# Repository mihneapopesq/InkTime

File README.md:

# InkTime

## Block Diagram
The system architecture centers on the nRF52840 SoC for wireless connectivity, with power stabilized at 3.3V via an RT6160 buck-boost regulator. It integrates a LiPo battery with USB-C charging alongside an e-paper display, IMU, fuel gauge, and haptic feedback.

## Bill of Materials (BOM)

|Component|JLC Part #|Package|Description|Datasheet|
| :--- | :--- | :--- | :--- | :--- |
|SJ1|N/A|Solder Jumper (Copper feature - leave open)|SMD solder JUMPER|N/A|
|R2, R3, R4|[C3920633](https://www.lcsc.com/product-detail/C3920633.html)|0201|7.68k 0201 Thin Film Surface Mount Fixed Resistor +/-0.5% 0.031W CPF0201D7K68C1|[datasheet](https://wmsc.lcsc.com/wmsc/upload/file/pdf/v2/lcsc/2404081048_TE-Connectivity-CPF0201B511RE1_C3920633.pdf)|
|C23, C27, C34, C42|[C21012218](https://www.lcsc.com/product-detail/C21012218.html)|-|Check availability|[datasheet](https://jlc-prod-smt.oss-eu-central-1.aliyuncs.com/smtDataManualFile/8603520985945550848-C21012218.pdf?response-content-disposition=attachment%3B%20filename%3DC21012218.pdf%3B%20filename%2A%3DUTF-8%27%27C21012218.pdf&x-oss-date=20260407T205848Z&x-oss-expires=1800&x-oss-security-token=CAISgAN1q6Ft5B2yfSjIr5r9Dd2HhJt1xpCRZnzhgHQ0Psp9nrTKiTz2IHhMdHJsAOodtv0%2FmmhT6PkclqRLcbhpcmfjV%2BZHzLB8qYoRtS1%2F4J7b16cNrbH4M4H6aXeirtuwDsz9SNTCALjPD3nPii50x5bjaDymRCbLGJaViJlhHLN1Ow6jdmhpCctxLAlvo9NgFxm3D%2Fu2NQPwiWf9FVdhvhEG6Vly8qOi2MaRmFy8yFTx0b0SvJ%2BjYMrmPctoN9JnSdC5mfdzau3a1TJ84gRD0a5wkaVA1zbDs5bfISEIuUzebreLqY03dV4mOvdqIcMe8qigz88fk%2FfIioH6xyxKOexoSCnFTOiiupCcQLPyao9jLu6iayqViY7QaIOTqQohZmkAMwVOasAsI3Ngh4zF97Qt0cVNkXO9gWfLI8DtuMleWoolCMBMoNHD0eS19jklBdzSlusJRAJJUVBflCeKEaRNSAd3WGhEfM2%2BBt4QT30w5N2u00S8OSMIfXAg5qKWD5sagAGsz%2FZUSUxHdlmxVPmipF%2FTcZWs78wlHh10XRuVSQAFwkjbrT5Hik%2Bt6g43igoBe9p%2FcAdU6beRw%2F0OV8Ul08RsL45K5wTZwHFsbzFcwqB3eAqV0VruhFdx%2FHGC73AK3f%2BS3e6Qh1%2F1xoEQbmetO%2F%2BEcdyt%2BmwKiZrCa5Agq9keuCAA&x-oss-signature-version=OSS4-HMAC-SHA256&x-oss-credential=STS.NYHFg3iDTqRzdZPdta2EQqqak%2F20260407%2Feu-central-1%2Foss%2Faliyun_v4_request&x-oss-signature=20ddec61a1b664f2d44439cb342bbd932d8702b658f2816e0dfb7eb77563430a)|
|EPD_C5|[C9900156064](https://www.lcsc.com/product-detail/C9900156064.html)|201|Generic chip capacitor|[datasheet](https://ds.yuden.co.jp/TYCOMPAS/or/download?pn=MLAST063SCG681JFNA01&fileType=CA)|
|R1_EP_DR|[C3920633](https://www.lcsc.com/product-detail/C3920633.html)|0201|7.68k 0201 Thin Film Surface Mount Fixed Resistor +/-0.5% 0.031W CPF0201D7K68C1|[datasheet](https://wmsc.lcsc.com/wmsc/upload/file/pdf/v2/lcsc/2404081048_TE-Connectivity-CPF0201B511RE1_C3920633.pdf)|
|C15|[C9900156064](https://www.lcsc.com/product-detail/C9900156064.html)|201|Generic chip capacitor|[datasheet](https://ds.yuden.co.jp/TYCOMPAS/or/download?pn=MLAST063SCG681JFNA01&fileType=CA)|
|C5, C7, C8, C12, C19|[C9900156064](https://www.lcsc.com/product-detail/C9900156064.html)|201|Generic chip capacitor|[datasheet](https://ds.yuden.co.jp/TYCOMPAS/or/download?pn=MLAST063SCG681JFNA01&fileType=CA)|
|C11|[C9900156064](https://www.lcsc.com/product-detail/C9900156064.html)|201|Generic chip capacitor|[datasheet](https://ds.yuden.co.jp/TYCOMPAS/or/download?pn=MLAST063SCG681JFNA01&fileType=CA)|
|R2_EP_DR, R9, R_PWR_EPD|[C3920633](https://www.lcsc.com/product-detail/C3920633.html)|0201|7.68k 0201 Thin Film Surface Mount Fixed Resistor +/-0.5% 0.031W CPF0201D7K68C1|[datasheet](https://wmsc.lcsc.com/wmsc/upload/file/pdf/v2/lcsc/2404081048_TE-Connectivity-CPF0201B511RE1_C3920633.pdf)|
|R5, R7, R8|[C3920633](https://www.lcsc.com/product-detail/C3920633.html)|0201|7.68k 0201 Thin Film Surface Mount Fixed Resistor +/-0.5% 0.031W CPF0201D7K68C1|[datasheet](https://wmsc.lcsc.com/wmsc/upload/file/pdf/v2/lcsc/2404081048_TE-Connectivity-CPF0201B511RE1_C3920633.pdf)|
|C1-EP-DR|[C9900156064](https://www.lcsc.com/product-detail/C9900156064.html)|201|Generic chip capacitor|[datasheet](https://ds.yuden.co.jp/TYCOMPAS/or/download?pn=MLAST063SCG681JFNA01&fileType=CA)|
|C24, C39|[C9900179830](https://www.lcsc.com/product-detail/C9900179830.html)|402|0402 (1005 Metric)|N/A|
|L2|[C12669](https://www.lcsc.com/product-detail/C12669.html)|402|Generic chip inductor|[datasheet](https://www.lcsc.com/datasheet/lcsc_datasheet_2304140030_Murata-Electronics-LQG15HS27NJ02D_C12669.pdf)|
|C1, C2, C17, C18|[C9900156064](https://www.lcsc.com/product-detail/C9900156064.html)|201|Generic chip capacitor|[datasheet](https://ds.yuden.co.jp/TYCOMPAS/or/download?pn=MLAST063SCG681JFNA01&fileType=CA)|
|L3|[C12669](https://www.lcsc.com/product-detail/C12669.html)|402|Generic chip inductor|[datasheet](https://www.lcsc.com/datasheet/lcsc_datasheet_2304140030_Murata-Electronics-LQG15HS27NJ02D_C12669.pdf)|
|C3, C4|[C9900156064](https://www.lcsc.com/product-detail/C9900156064.html)|201|Generic chip capacitor|[datasheet](https://ds.yuden.co.jp/TYCOMPAS/or/download?pn=MLAST063SCG681JFNA01&fileType=CA)|
|C29, C30, C31, C32, C37, C38|[C3920633](https://www.lcsc.com/product-detail/C3920633.html)|0201|7.68k 0201 Thin Film Surface Mount Fixed Resistor +/-0.5% 0.031W CPF0201D7K68C1|[datasheet](https://wmsc.lcsc.com/wmsc/upload/file/pdf/v2/lcsc/2404081048_TE-Connectivity-CPF0201B511RE1_C3920633.pdf)|
|EPD_C1, EPD_C2, EPD_C6, EPD_C7, EPD_C8, EPD_C9, EPD_C10, EPD_C11, EPD_C12|[C9900156064](https://www.lcsc.com/product-detail/C9900156064.html)|201|Generic chip capacitor|[datasheet](https://ds.yuden.co.jp/TYCOMPAS/or/download?pn=MLAST063SCG681JFNA01&fileType=CA)|
|R_TYPE_SEL|[C3920633](https://www.lcsc.com/product-detail/C3920633.html)|0201|7.68k 0201 Thin Film Surface Mount Fixed Resistor +/-0.5% 0.031W CPF0201D7K68C1|[datasheet](https://wmsc.lcsc.com/wmsc/upload/file/pdf/v2/lcsc/2404081048_TE-Connectivity-CPF0201B511RE1_C3920633.pdf)|
|SW_DN, SW_ENT, SW_UP|[C569760](https://www.lcsc.com/product-detail/C569760.html)|SMD,3.9x2.9mm|-40℃~+85℃ 1.6N 1.6mm 15V 2.9mm 20mA 3.9mm 500,000 Cycles IP67 J-Lead Rectangular Button SPST Surface Mount,Vertical White With Bracket SMD,3.9x2.9mm Tactile Switches ROHS|[datasheet](https://wmsc.lcsc.com/wmsc/upload/file/pdf/v2/lcsc/2301111010_PANASONIC-EVPAKE31A_C569760.pdf)|
|Q1|[C2564](https://www.lcsc.com/product-detail/C2564.html)|TO-220AB|-55℃~+175℃ 1 P-Channel 180nC@10V 200W 20mΩ@10V 3.4nF 4V 55V 640pF 74A P-Channel TO-220AB MOSFETs ROHS|[datasheet](https://www.lcsc.com/datasheet/lcsc_datasheet_1809041724_Infineon-Technologies-IRF4905PBF_C2564.pdf)|
|C25, C33|[C9900179830](https://www.lcsc.com/product-detail/C9900179830.html)|402|0402 (1005 Metric)|N/A|
|ANT1|[C2917717](https://www.lcsc.com/product-detail/C2917717.html)|1206|-45℃~+125℃ 0.5dBi 1.3mm 1.6mm 100MHz 2.45GHz 2W 3.2mm 50Ω Patch Antenna 1206 Antennas ROHS|[datasheet](https://www.lcsc.com/datasheet/lcsc_datasheet_2404021210_Johanson-Dielectrics-2450AT18B100E_C2917717.pdf)|
|L1|[C12669](https://www.lcsc.com/product-detail/C12669.html)|402|Generic chip inductor|[datasheet](https://www.lcsc.com/datasheet/lcsc_datasheet_2304140030_Murata-Electronics-LQG15HS27NJ02D_C12669.pdf)|
|X2|[C32346](https://www.lcsc.com/product-detail/C32346.html)|SMD3215-2P|-40℃~+85℃ 12.5pF 32.768kHz 70kΩ Crystal Oscillator ±20ppm SMD3215-2P Crystals ROHS|[datasheet](https://www.lcsc.com/datasheet/lcsc_datasheet_2404180925_Seiko-Epson-Q13FC13500004_C32346.pdf)|
|X1|[C9009](https://www.lcsc.com/product-detail/C9009.html)|SMD3225-4P|-40℃~+85℃ 12pF 32MHz Crystal Oscillator ±10ppm ±20ppm SMD3225-4P Crystals ROHS|[datasheet](https://www.lcsc.com/datasheet/lcsc_datasheet_2403291504_YXC-Crystal-Oscillators-X322532MOB4SI_C9009.pdf)|
|R17, R18|[C3920633](https://www.lcsc.com/product-detail/C3920633.html)|0201|7.68k 0201 Thin Film Surface Mount Fixed Resistor +/-0.5% 0.031W CPF0201D7K68C1|[datasheet](https://wmsc.lcsc.com/wmsc/upload/file/pdf/v2/lcsc/2404081048_TE-Connectivity-CPF0201B511RE1_C3920633.pdf)|
|C43|[C9900156064](https://www.lcsc.com/product-detail/C9900156064.html)|201|Generic chip capacitor|[datasheet](https://ds.yuden.co.jp/TYCOMPAS/or/download?pn=MLAST063SCG681JFNA01&fileType=CA)|
|C2-EP-DR|[C9900156064](https://www.lcsc.com/product-detail/C9900156064.html)|201|Generic chip capacitor|[datasheet](https://ds.yuden.co.jp/TYCOMPAS/or/download?pn=MLAST063SCG681JFNA01&fileType=CA)|
|C6, C14, C20, C21|[C9900156064](https://www.lcsc.com/product-detail/C9900156064.html)|201|Generic chip capacitor|[datasheet](https://ds.yuden.co.jp/TYCOMPAS/or/download?pn=MLAST063SCG681JFNA01&fileType=CA)|
|C16|[C9900156064](https://www.lcsc.com/product-detail/C9900156064.html)|201|Generic chip capacitor|[datasheet](https://ds.yuden.co.jp/TYCOMPAS/or/download?pn=MLAST063SCG681JFNA01&fileType=CA)|
|J1|[C122434](https://www.lcsc.com/product-detail/C122434.html)|SMD,P=0.5mm,Surface Mount，Right Angle|FFC & FPC Connectors 0.5mm FPC RA SMT Dual Contact 24Ckt|[datasheet](https://www.molex.com/content/dam/molex/molex-dot-com/products/automated/en-us/salesdrawingpdf/503/503480/5034802400_sd.pdf)|
|R1_USB, R2_USB|[C3920633](https://www.lcsc.com/product-detail/C3920633.html)|0201|7.68k 0201 Thin Film Surface Mount Fixed Resistor +/-0.5% 0.031W CPF0201D7K68C1|[datasheet](https://wmsc.lcsc.com/wmsc/upload/file/pdf/v2/lcsc/2404081048_TE-Connectivity-CPF0201B511RE1_C3920633.pdf)|
|L5|[C1329646](https://www.lcsc.com/product-detail/C1329646.html)|SMD,4.8x4.8mm|1.6A 1.6A 4.7uH 41.4mΩ AEC-Q200 ±30% SMD,4.8x4.8mm Power Inductors ROHS|[datasheet](https://wmsc.lcsc.com/wmsc/upload/file/pdf/v2/lcsc/2304140030_BOURNS-SRR4828A-4R7Y_C1329646.pdf)|
|C9|[C9900156064](https://www.lcsc.com/product-detail/C9900156064.html)|201|Generic chip capacitor|[datasheet](https://ds.yuden.co.jp/TYCOMPAS/or/download?pn=MLAST063SCG681JFNA01&fileType=CA)|
|IC3|[C189517](https://www.lcsc.com/product-detail/C189517.html)|LGA-12(2x2)|Accelerometers Triaxial low-g 12bit Acceleration Sensor|[datasheet](https://www.lcsc.com/datasheet/C189517.pdf)|
|IC1|[C3682423](https://www.lcsc.com/product-detail/C3682423.html)|DSBGA-8(1.1x1.6)|Charger IC Lithium Ion/Polymer, Lithium Iron Phosphate 8-DSBGA (1.6x1.1)|[datasheet](https://www.ti.com/cn/lit/ds/symlink/bq25180.pdf?ts=1775594237116)|
|IC2|[C81079](https://www.lcsc.com/product-detail/C81079.html)|DSBGA-9|Haptic Driver for ERM/LRA with Built-In Library and Smart Loop Architecture|[datasheet](https://www.ti.com/cn/lit/gpn/drv2605)|
|L7|[C5832368](https://www.lcsc.com/product-detail/C5832368.html)|1008|13mΩ 470nH 6.5A 7.5A ±20% 1008 Power Inductors ROHS|[datasheet](https://wmsc.lcsc.com/wmsc/upload/file/pdf/v2/lcsc/2306021632_cjiang--Changjiang-Microelectronics-Tech-FTC252012SR47MBCA_C5832368.pdf)|
|TP (Test Pads)|N/A|N/A|Test pad|N/A|
|J4|[C709357](https://www.lcsc.com/product-detail/C709357.html)|SMD|-40℃~+85℃ 1 10,000 cycles 16P 30V 3A 7.81mm Female Surface Mount, Right Angle Type-C SMD USB Connectors ROHS|[datasheet](https://www.lcsc.com/datasheet/lcsc_datasheet_2404191039_Shenzhen-Kinghelm-Elec-KH-TYPE-C-16P_C709357.pdf)|
|U2|[C2682616](https://www.lcsc.com/product-detail/C2682616.html)|DFN-8-EP(2x2)|-40℃~+85℃ 1 2.5V~4.5V 3uA I2C Lithium Battery DFN-8-EP(2x2) Battery Management ROHS|[datasheet](https://www.lcsc.com/datasheet/lcsc_datasheet_2410121738_Analog-Devices-Inc--Maxim-Integrated-MAX17048G-T10_C2682616.pdf)|
|D2, D4, D5|[C82046](https://www.lcsc.com/product-detail/C82046.html)|SOD-123|ON SEMICONDUCTOR - MBR0530 - DIODE, SCHOTTKY, 0.5A, 30V, SOD-123|[datasheet](https://www.lcsc.com/datasheet/lcsc_datasheet_2304140030_onsemi-MBR0530T1G_C82046.pdf)|
|C10, C13, C22|[C9900156064](https://www.lcsc.com/product-detail/C9900156064.html)|201|Generic chip capacitor|[datasheet](https://ds.yuden.co.jp/TYCOMPAS/or/download?pn=MLAST063SCG681JFNA01&fileType=CA)|
|U1|[C3606653](https://www.lcsc.com/product-detail/C3606653.html)|QFN-48(6x6)|nRF52840|[datasheet](https://www.lcsc.com/datasheet/C3606653.pdf)|
|IC9|[C7065276](https://www.lcsc.com/product-detail/C7065276.html)|WLCSP-15B(2.3x1.4)|Buck-Boost Regulator Positive Output Step-Up/Step-Down I2C DC-DC Controller IC 15-WL-CSP (BSC) (1.4x2.3)|[datasheet](https://wmsc.lcsc.com/wmsc/upload/file/pdf/v2/lcsc/2312271436_Richtek-Tech-RT6160AWSC_C7065276.pdf)|
|Q3|[C469327](https://www.lcsc.com/product-detail/C469327.html)|SOT-323|MOSFET N-Ch 30V 1.5A TrenchFET SC70 Vishay Si1308EDL-T1-GE3 N-channel MOSFET Transistor, 1.5 A, 30 V, 3-Pin SC-70|[datasheet](https://www.lcsc.com/datasheet/lcsc_datasheet_1912202016_Vishay-Intertech-SI1308EDL-T1-GE3_C469327.pdf)|
|J2|[C90533](https://www.lcsc.com/product-detail/C90533.html)|P=1mm|CABLE ADAPTER 6 POS|[datasheet](https://wmsc.lcsc.com/wmsc/upload/file/pdf/v2/lcsc/1810141506_LX-FFC6P1-0mm7CM_C90533.pdf)|
|D3|[C2969755](https://www.lcsc.com/product-detail/C2969755.html)|SOT-23-6L|Low Cap. ESD Protection Auto SOT-23-6 STMicroelectronics USBLC6-2SC6Y, Dual Uni-Directional TVS Diode Array, 6-Pin SOT-23|[datasheet](https://wmsc.lcsc.com/wmsc/upload/file/pdf/v2/lcsc/2211080730_STMicroelectronics-USBLC6-2SC6Y_C2969755.pdf)|

## Hardware Functionality & Technical Architecture

The **InkTime** platform is an ultra-low-power wearable built around the **Nordic nRF52840 SoC**. The design focuses on maximizing battery autonomy through an E-Ink interface and advanced power management, ensuring the device remains functional for weeks on a single charge.

### 1. Core Processing Unit
The **nRF52840 (ARM Cortex-M4F @ 64 MHz)** serves as the system's brain. It was selected for its:
* **Connectivity:** Native Bluetooth 5.4 LE support for smartphone syncing.
* **I/O Versatility:** Integrated USB, SPI, and I2C peripherals to manage all sub-systems.
* **Efficiency:** Advanced "Deep Sleep" modes (sub-10 µA) and a dedicated 32.768 kHz crystal for accurate low-power timing.

### 2. Power & Energy Management
The power tree is designed to extract maximum energy from the **250 mAh Li-Po battery**:
* **Charging:** A **BQ25180 PMIC** manages the CC/CV charging cycle via **USB-C**, providing overvoltage and thermal protection.
* **Regulation:** The **RT6160 Buck-Boost converter** maintains a stable **3.3V** rail even as the battery voltage drops toward 3.0V, outperforming standard LDOs.
* **Fuel Gauge:** The **MAX17048G** monitor provides high-precision State of Charge (SoC) data via I2C, allowing for accurate battery percentage alerts.

### 3. Peripherals and User Interface
* **E-Paper Display (1.54"):** Connected via a 24-pin FPC (SPI). It draws power only during refreshes, making it ideal for static data. A dedicated driving circuit with MOSFETs and Schottky diodes manages the necessary bias voltages.
* **Motion Sensing:** The **BMA423 IMU (I2C)** enables "wrist-tilt" wake-up and step counting, allowing the MCU to stay in sleep mode until motion is detected.
* **Haptic Feedback:** The **DRV2605 driver** handles the vibration motor (shaker), offloading PWM waveform generation from the MCU for crisp, customizable alerts.
* **User Input:** Three physical buttons (`SW_UP`, `SW_ENT`, `SW_DN`) provide a reliable navigation interface.

### 4. Power Profile & Autonomy
With an average current draw ($I_{avg}$) of approximately **180 µA** (combining deep sleep, sensor polling, and periodic display updates), the theoretical autonomy is:

$$T = \frac{250\text{ mAh}}{0.18\text{ mA}} \approx 1389\text{ hours}$$

In real-world scenarios, this translates to an estimated **10–14 days** of continuous operation.

## nRF52840 Signal Assignment & Connectivity

| Pin(s) | Peripheral | Function | Justification |
| :--- | :--- | :--- | :--- |
| **P0.02** | SPI SCK | Clock | SPI clock for the E-Ink display interface. |
| **P0.03** | SPI MOSI | Data | Master Out Slave In; sends pixel data to display. |
| **P0.05** | EPD CS | Chip Select | Active-low signal to enable SPI display communication. |
| **P0.15** | EPD DC | Control | Toggles between Data and Command modes for E-Ink. |
| **P0.16** | EPD RST | Control | Provides a hardware reset path for the display. |
| **P0.17** | EPD BUSY | Status Input | Hardware flag indicating active display refresh cycles. |
| **P0.06** | I2C SDA | Data | Serial Data line shared by IMU, Fuel Gauge, and Haptics. |
| **P0.07** | I2C SCL | Clock | Serial Clock line for the high-speed I2C bus. |
| **P0.08** | IMU INT1 | Interrupt | Primary motion/event trigger from BMA421/BMA423. |
| **P1.08** | IMU INT2 | Interrupt | Secondary interrupt line for advanced motion features. |
| **P0.09** | Fuel Gauge ALERT | Interrupt | Real-time battery status alert from MAX17048. |
| **P0.11** | PMIC INT | Interrupt | Fault or charging status update from BQ25180. |
| **P0.12** | HAPTIC_EN | Control | Master enable signal for the DRV2605 haptic driver. |
| **P0.13** | Button UP | GPIO Input | Digital input for the 'Up' navigation switch. |
| **P0.14** | Button ENTER | GPIO Input | Digital input for the 'Enter/Select' switch. |
| **P1.02** | Button DOWN | GPIO Input | Digital input for the 'Down' navigation switch. |
| **P0.18** | nRESET | Reset | System hardware reset (Reset pin). |
| **D+ / D-** | USB Interface | USB Data | Dedicated lines for USB communication and charging. |
| **SWDIO** | Debug Port | Data | Serial Wire Debug bidirectional data line. |
| **SWDCLK** | Debug Port | Clock | Serial Wire Debug clock reference. |

## Design Log & Validation

### 1. Engineering Decisions
* **Density:** Used **0201 passives** and **1.0 mm PCB thickness** to fit all 49 components on the **TOP layer** within the compact enclosure.
* **RF Performance:** Maintained a strict **copper-free keep-out zone** under the 2.4 GHz antenna and used **via stitching** to stabilize the ground planes.
* **Routing:** Power lines are **0.3 mm** for stability, while data lines are **0.15 mm**. Decoupling caps are placed within **0.5 mm** of IC pins to minimize noise.

### 2. Approved Errors (DRC & ERC)
The following warnings were manually verified and intentionally accepted:

| Error Type | Reason for Approval |
| :--- | :--- |
| **DRC: Dimensions** | Button and USB-C placement is fixed by the **mechanical cutouts** of the 3D-printed case. |
| **DRC: Overlap** | Caused by **via-in-pad / escape routing** (0.15mm vias). Necessary for the dense fanout of the nRF52840. |
| **ERC: Input Pins Only** | Verified manually; all nets are functionally connected despite the CAD warning. |
| **ERC: Power Pins** | Confirmed that all supply rails (3V3, VBAT) are correctly routed to their regulators. |

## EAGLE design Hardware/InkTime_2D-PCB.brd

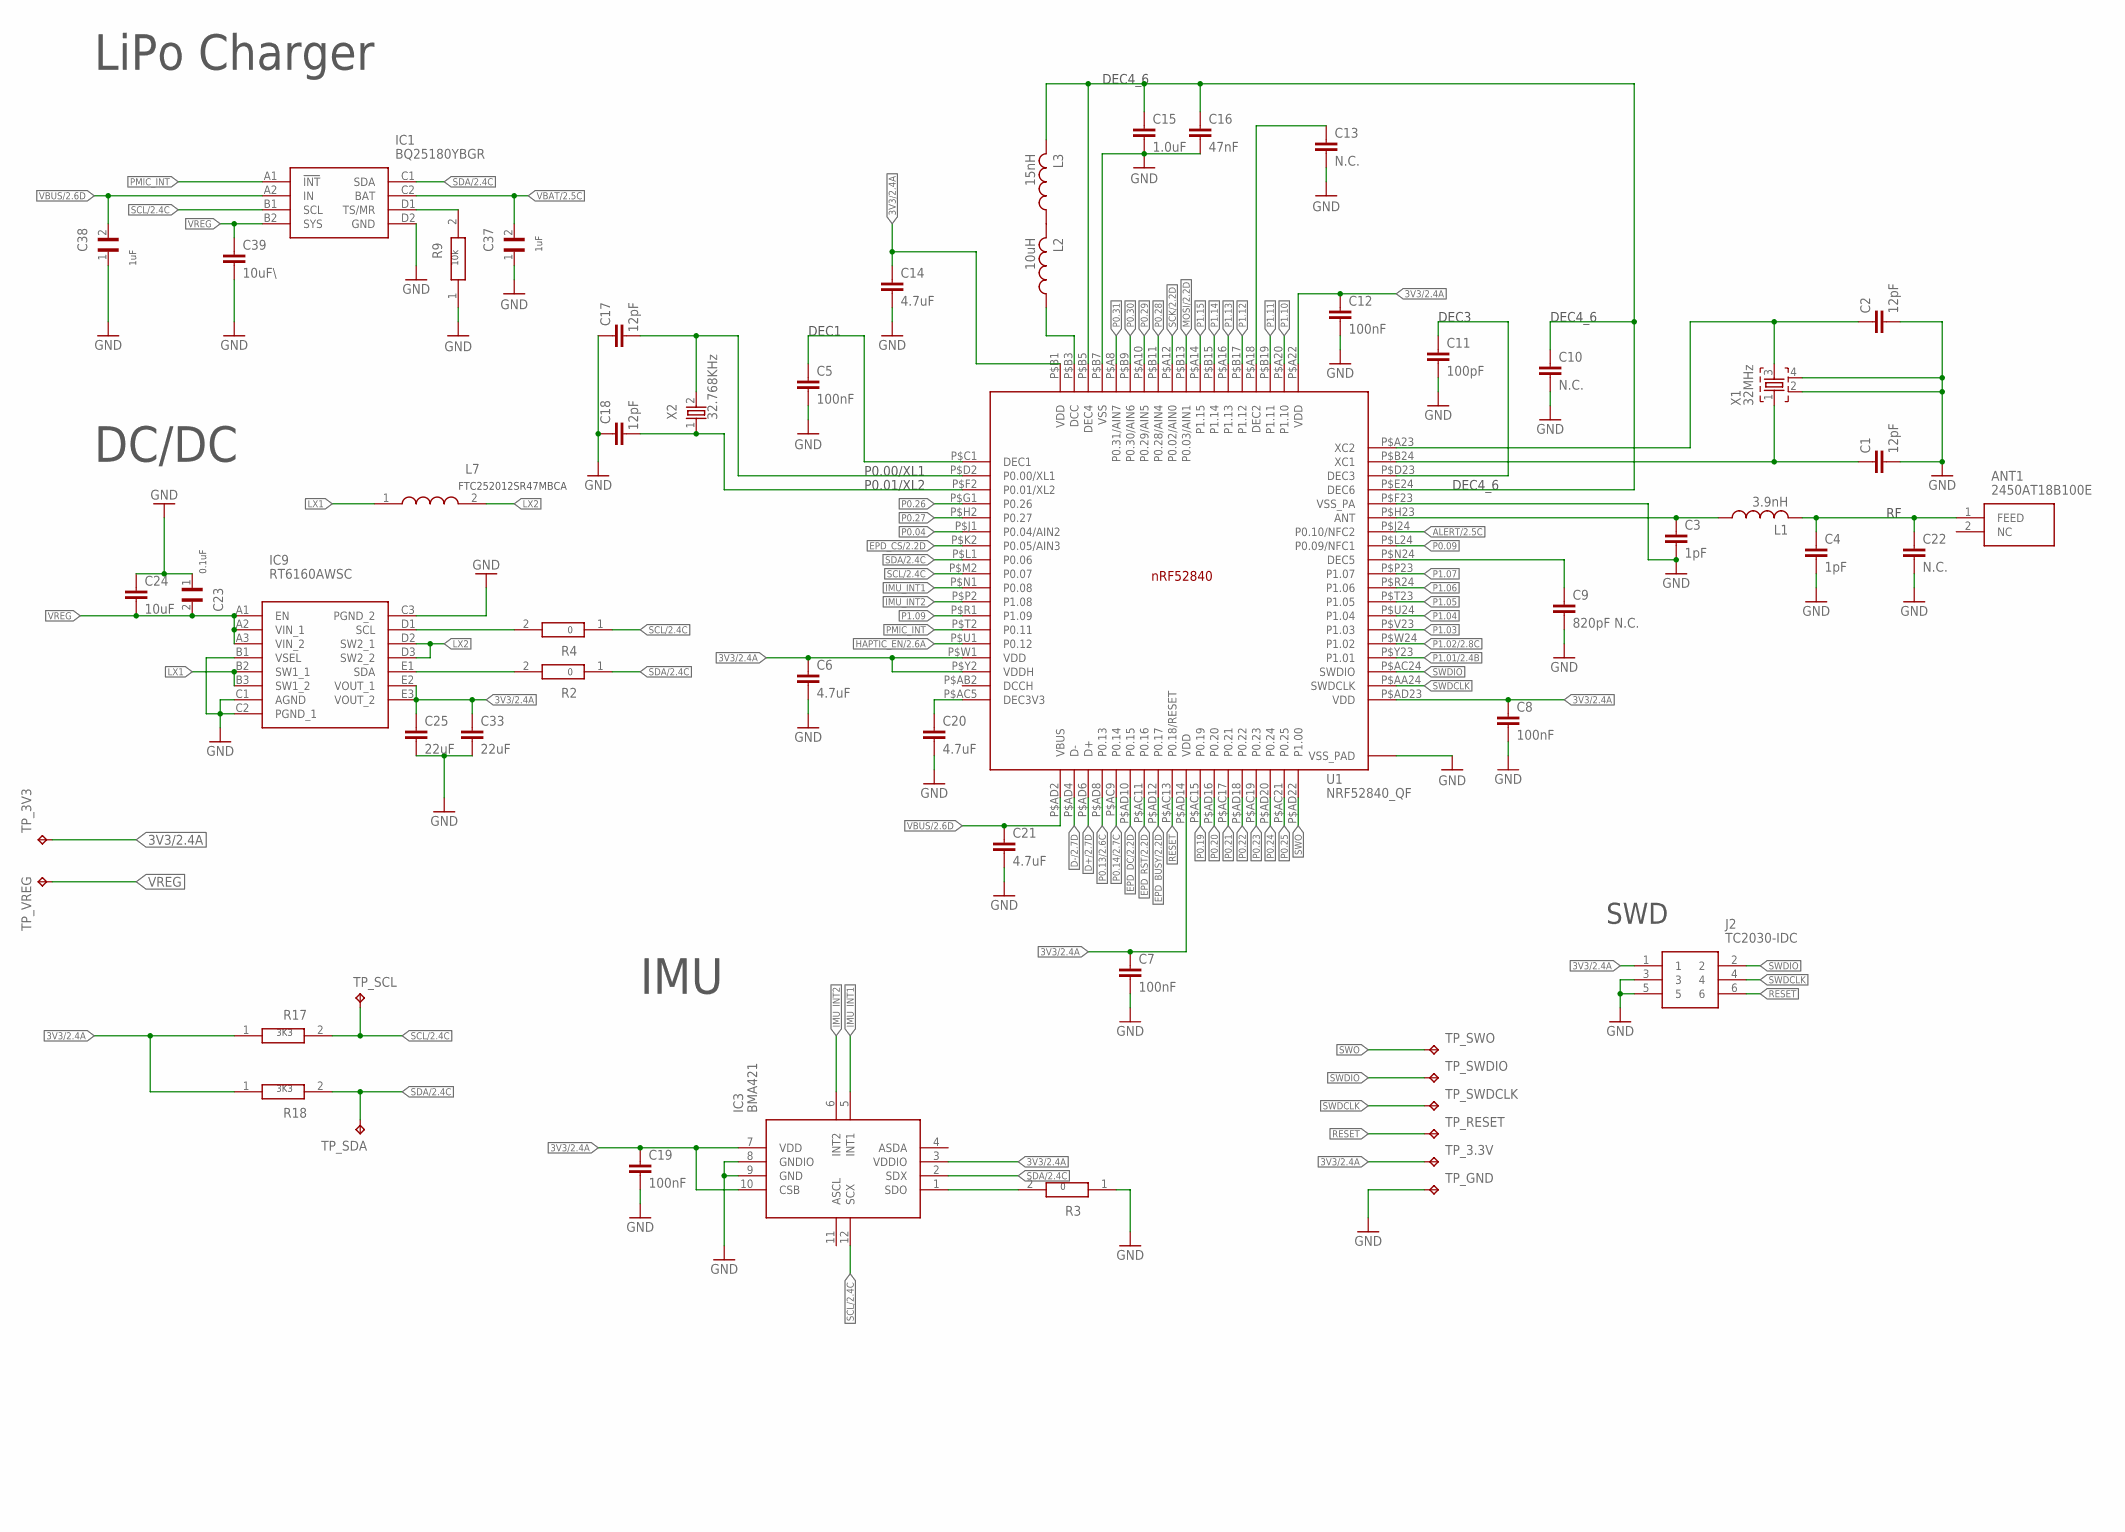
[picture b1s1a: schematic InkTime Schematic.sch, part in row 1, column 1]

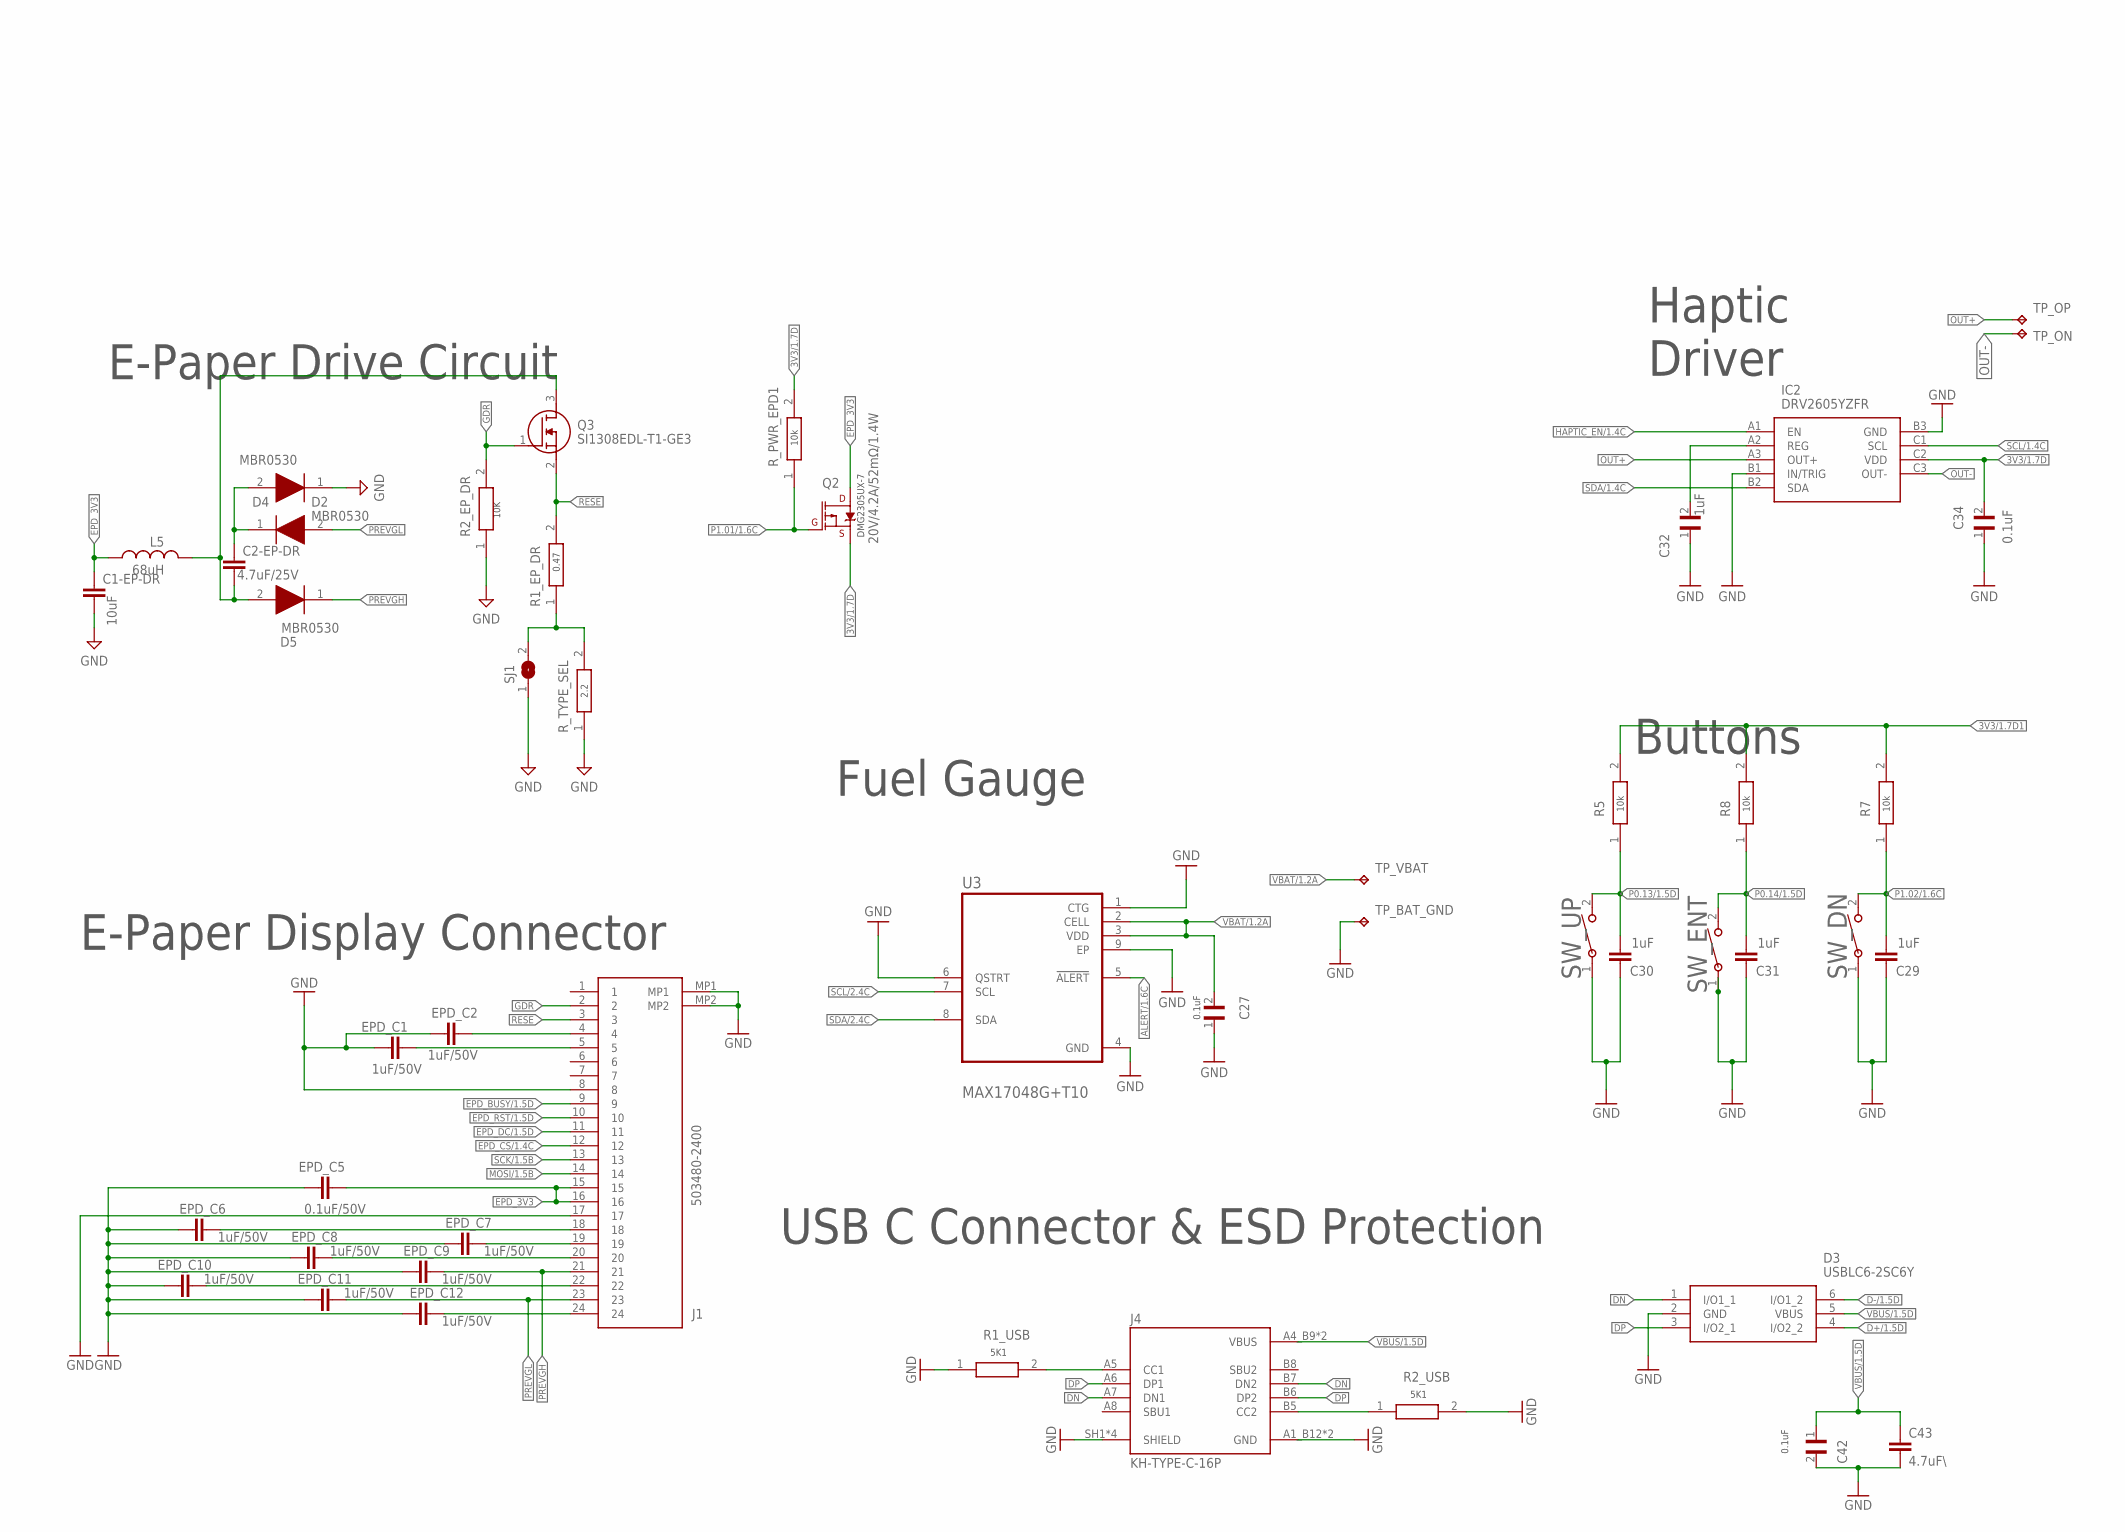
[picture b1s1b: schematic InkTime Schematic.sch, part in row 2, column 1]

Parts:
ANT1: 2450AT18B100E; 2450AT18B100E_ANTC3216X140N
C1, C2, C17, C18: 12pF; NORDIC_NRF_3_RESC0201_L
C1-EP-DR: 10uF; NORDIC_NRF_3_RESC0402_L
C2-EP-DR: 4.7uF/25V; NORDIC_NRF_3_RESC0402_L
C3, C4: 1pF; NORDIC_NRF_3_RESC0201_L
C5, C7, C8, C12, C19: 100nF; NORDIC_NRF_3_RESC0201_L
C6, C14, C20, C21: 4.7uF; NORDIC_NRF_3_RESC0402_L
C9: 820pF N.C.; NORDIC_NRF_3_RESC0201_L
C10, C13, C22: N.C.; NORDIC_NRF_3_RESC0201_L
C11: 100pF; NORDIC_NRF_3_RESC0201_L
C15: 1.0uF; NORDIC_NRF_3_RESC0402_L
C16: 47nF; NORDIC_NRF_3_RESC0201_L
C23, C27, C34: 0.1uF; GRM011R60J152KE01L_1_0201
C24: 10uF; PERFECT_0402_0402
C25, C33: 22uF; NORDIC_NRF_3_RESC0402_L
C29, C30, C31: 1uF; NORDIC_NRF_3_RESC0402_L
C32, C37, C38: 1uF; GRM011R60J152KE01L_1_0201
C39: 10uF\; NORDIC_NRF_3_RESC0402_L
C42: 0.1uF; GRM011R60J152KE01L_2_CAPC0201X13N
C43: 4.7uF\; NORDIC_NRF_3_RESC0402_L
D2, D4, D5: MBR0530; ESP32_C6_LIBRARY_5_SOD3716X135N
D3: USBLC6-2SC6Y; ESP32_C6_LIBRARY_3_SOT95P280X145-6N
EPD_C1, EPD_C2, EPD_C6, EPD_C7, EPD_C8, EPD_C9, EPD_C10, EPD_C11, EPD_C12: 1uF/50V; NORDIC_NRF_3_RESC0402_L
EPD_C5: 0.1uF/50V; NORDIC_NRF_3_RESC0201_L
IC1: BQ25180YBGR; BQ25180YBGR_BGA8C40P2X4_100X155X50
IC2: DRV2605YZFR; DRV2605YZFR_BGA9C50P3X3_144X144X62
IC3: BMA421; BMA423_BMA423
IC9: RT6160AWSC; RT6160AWSC_BGA15C40P3X5_140X230X60
J1: 503480-2400; 503480-2400_5034802400
J2: TC2030-IDC; TC2030-IDC_TC2030IDC
J4: KH-TYPE-C-16P; KH-TYPE-C-16P_KINGHELM_KH-TYPE-C-16P
L1: 3.9nH; NORDIC_NRF_2_RESC0201_L
L2: 10uH; NORDIC_NRF_2_RESC0201_L
L3: 15nH; NORDIC_NRF_2_RESC0201_L
L5: 68uH; NORDIC_NRF_2_RESC0402_L
L7: FTC252012SR47MBCA; MLP2016SR47MT0S1_INDC2016X100N
Q2: 20V/4.2A/52mΩ/1.4W; ESP32_C6_LIBRARY_4_ESP32_C6_LIBRARY_4_ESP32_C6_LIBRARY_4_ES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
Q3: SI1308EDL-T1-GE3; ESP32_C6_LIBRARY_6_SOT65P210X110-3N
R1_EP_DR: 0.47; CPF0201D7K68C1_0201
R1_USB, R2_USB: 5K1; CPF0201D7K68C1_0201
R2, R3, R4: 0; CPF0201D7K68C1_0201
R2_EP_DR: 10K; CPF0201D7K68C1_0201
R5, R7, R8: CPF0201D7K68C1_CPF0201D7K68C1; CPF0201D7K68C1_0201
R9: 10K; ERA-1AEB3401C_0201
R17, R18: 3K3; CPF0201D7K68C1_0201
R_PWR_EPD1: 10K; CPF0201D7K68C1_0201
R_TYPE_SEL: 2.2; CPF0201D7K68C1_0201
SJ1: ESP32_C6_LIBRARY_7_JUMPER_SJ
SW_DN: 2025-10-22_07-23-44_LIBRARY_EVP-AKE31ASW_EVP-AKE3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; 2025-10-22_07-23-44_LIBRARY_SW_EVP-AKE31A_PAN
SW_ENT: 2025-10-22_07-23-44_LIBRARY_EVP-AKE31ASW_EVP-AKE3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; 2025-10-22_07-23-44_LIBRARY_SW_EVP-AKE31A_PAN
SW_UP: 2025-10-22_07-23-44_LIBRARY_EVP-AKE31ASW_EVP-AKE3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; 2025-10-22_07-23-44_LIBRARY_SW_EVP-AKE31A_PAN
TP_3.3V, TP_3V3: HECTOR_WATCH_1_TPTP20R; HECTOR_WATCH_1_TP20R
TP_BAT_GND: HECTOR_WATCH_1_TPTP20R; HECTOR_WATCH_1_TP20R
TP_GND: HECTOR_WATCH_1_TPTP20R; HECTOR_WATCH_1_TP20R
TP_ON: HECTOR_WATCH_1_TPTP20R; HECTOR_WATCH_1_TP20R
TP_OP: HECTOR_WATCH_1_TPTP20R; HECTOR_WATCH_1_TP20R
TP_RESET: HECTOR_WATCH_1_TPTP20R; HECTOR_WATCH_1_TP20R
TP_SCL: HECTOR_WATCH_1_TPTP20R; HECTOR_WATCH_1_TP20R
TP_SDA: HECTOR_WATCH_1_TPTP20R; HECTOR_WATCH_1_TP20R
TP_SWDCLK: HECTOR_WATCH_1_TPTP20R; HECTOR_WATCH_1_TP20R
TP_SWDIO: HECTOR_WATCH_1_TPTP20R; HECTOR_WATCH_1_TP20R
TP_SWO: HECTOR_WATCH_1_TPTP20R; HECTOR_WATCH_1_TP20R
TP_VBAT: HECTOR_WATCH_1_TPTP20R; HECTOR_WATCH_1_TP20R
TP_VREG: HECTOR_WATCH_1_TPTP20R; HECTOR_WATCH_1_TP20R
U1: NRF52840_QF; NORDIC_NRF_4_AQFN50P700X700X85_HS-74N
U3: MAX17048G+T10; ESP32_C6_LIBRARY_SON50P200X200X80-9N
X1: 32MHz; NORDIC_NRF_BT-XTAL_2016_N
X2: 32.768KHz; NORDIC_NRF_1_XTAL_3215_N

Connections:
3V3/1.7D: C34.2, IC2.C2 (VDD), Q2.2 (S), R_PWR_EPD1.2
3V3/1.7D1: R5.2, R7.2, R8.2
3V3/2.4A: C6.1, C7.1, C8.1, C12.1, C14.1, C19.1, C25.1, C33.1, IC3.3 (VDDIO), IC3.7 (VDD), IC3.10 (CSB), IC9.E2 (VOUT_1), IC9.E3 (VOUT_2), J2.1, R17.1, R18.1, TP_3.3V.TP, TP_3V3.TP, U1.P$A22 (VDD), U1.P$AD14 (VDD), U1.P$AD23 (VDD), U1.P$B1 (VDD), U1.P$W1 (VDD), U1.P$Y2 (VDDH)
ALERT/1.6C: U3.5 (!ALERT)
ALERT/2.5C: U1.P$J24 (P0.10/NFC2)
D+/1.5D: D3.4 (I/O2_2)
D+/2.7D: U1.P$AD6 (D+)
D-/1.5D: D3.6 (I/O1_2)
D-/2.7D: U1.P$AD4 (D-)
DN: D3.1 (I/O1_1), J4.A7 (DN1), J4.B7 (DN2)
DP: D3.3 (I/O2_1), J4.A6 (DP1), J4.B6 (DP2)
EPD_3V3: C1-EP-DR.1, EPD_C5.2, J1.15, J1.16, L5.1, Q2.3 (D)
EPD_BUSY/1.5D: J1.9
EPD_BUSY/2.2D: U1.P$AD12 (P0.17)
EPD_CS/1.4C: J1.12
EPD_CS/2.2D: U1.P$K2 (P0.05/AIN3)
EPD_DC/1.5D: J1.11
EPD_DC/2.2D: U1.P$AD10 (P0.15)
EPD_RST/1.5D: J1.10
EPD_RST/2.2D: U1.P$AC11 (P0.16)
GDR: J1.2, Q3.1 (G), R2_EP_DR.2
GND: C1.2, C1-EP-DR.2, C2.2, C3.2, C4.2, C5.2, C6.2, C7.2, C8.2, C9.2, C10.2, C11.2, C12.2, C13.2, C14.2, C15.2, C16.2, C17.2, C18.2, C19.2, C20.2, C21.2, C22.2, C23.1, C24.1, C25.2, C27.1, C29.1, C30.1, C31.1, C32.1, C33.2, C34.1, C37.1, C38.1, C39.2, C42.2, C43.2, D3.2 (GND), D4.1 (K), EPD_C1.1, EPD_C2.1, EPD_C5.1, EPD_C6.1, EPD_C7.1, EPD_C8.1, EPD_C9.1, EPD_C10.1, EPD_C11.1, EPD_C12.1, IC1.D2 (GND), IC2.B1 (IN/TRIG), IC2.B3 (GND), IC3.8 (GNDIO), IC3.9 (GND), IC9.B1 (VSEL), IC9.C1 (AGND), IC9.C2 (PGND_1), IC9.C3 (PGND_2), J1.8, J1.17, J1.MP1, J1.MP2, J2.3, J2.5, J4.A1_B12 (GND), J4.A12_B1 (GND), J4.SH1 (SHIELD), J4.SH2 (SHIELD), J4.SH3 (SHIELD), J4.SH4 (SHIELD), R1_USB.1, R2_EP_DR.1, R2_USB.2, R3.1, R9.1, SJ1.1, SW_DN.1, SW_ENT.1, SW_UP.1, TP_BAT_GND.TP, TP_GND.TP, U1.P$74 (VSS_PAD), U1.P$75 (VSS_PAD), U1.P$76 (VSS_PAD), U1.P$77 (VSS_PAD), U1.P$78 (VSS_PAD), U1.P$79 (VSS_PAD), U1.P$80 (VSS_PAD), U1.P$81 (VSS_PAD), U1.P$82 (VSS_PAD), U1.P$83 (VSS_PAD), U1.P$84 (VSS_PAD), U1.P$85 (VSS_PAD), U1.P$86 (VSS_PAD), U1.P$87 (VSS_PAD), U1.P$88 (VSS_PAD), U1.P$89 (VSS_PAD), U1.P$90 (VSS_PAD), U1.P$B7 (VSS), U1.P$F23 (VSS_PA), U3.1 (CTG), U3.4 (GND), U3.6 (QSTRT), U3.9 (EP), X1.2, X1.4
HAPTIC_EN/1.4C: IC2.A1 (EN)
HAPTIC_EN/2.6A: U1.P$U1 (P0.12)
IMU_INT1: IC3.5 (INT1), U1.P$N1 (P0.08)
IMU_INT2: IC3.6 (INT2), U1.P$P2 (P1.08)
LX1: IC9.B2 (SW1_1), IC9.B3 (SW1_2), L7.1
LX2: IC9.D2 (SW2_1), IC9.D3 (SW2_2), L7.2
MOSI/1.5B: J1.14
MOSI/2.2D: U1.P$B13 (P0.03/AIN1)
unnamed: C13.1, U1.P$A18 (DEC2)
unnamed: C20.1, U1.P$AC5 (DEC3V3)
unnamed: C9.1, U1.P$N24 (DEC5)
unnamed: L2.1, U1.P$B3 (DCC)
unnamed: L2.2, L3.1
unnamed: C10.1, C15.1, C16.1, L3.2, U1.P$B5 (DEC4), U1.P$E24 (DEC6)
unnamed: C5.1, U1.P$C1 (DEC1)
unnamed: C17.1, U1.P$D2 (P0.00/XL1), X2.2
unnamed: C18.1, U1.P$F2 (P0.01/XL2), X2.1
unnamed: C11.1, U1.P$D23 (DEC3)
unnamed: C2.1, U1.P$A23 (XC2), X1.3
unnamed: C1.1, U1.P$B24 (XC1), X1.1
unnamed: ANT1.1 (FEED), C4.1, C22.1, L1.2
unnamed: C3.1, L1.1, U1.P$H23 (ANT)
unnamed: IC9.D1 (SCL), R4.2
unnamed: IC9.E1 (SDA), R2.2
unnamed: IC1.D1 (TS/MR), R9.2
unnamed: EPD_C2.2, J1.4
unnamed: EPD_C1.2, J1.5
unnamed: EPD_C6.2, J1.18
unnamed: EPD_C7.2, J1.19
unnamed: EPD_C8.2, J1.20
unnamed: IC3.1 (SDO), R3.2
unnamed: EPD_C10.2, J1.22, R_TYPE_SEL.1
unnamed: EPD_C12.2, J1.24
unnamed: C32.2, IC2.A2 (REG)
unnamed: C2-EP-DR.2, D5.2 (A), L5.2, Q3.3 (D)
unnamed: C2-EP-DR.1, D2.1 (K), D4.2 (A)
unnamed: R1_EP_DR.1, R_TYPE_SEL.2, SJ1.2
unnamed: J4.A5 (CC1), R1_USB.2
unnamed: J4.B5 (CC2), R2_USB.1
OUT+: IC2.A3 (OUT+), TP_OP.TP
OUT-: IC2.C3 (OUT-), TP_ON.TP
P0.04: U1.P$J1 (P0.04/AIN2)
P0.09: U1.P$L24 (P0.09/NFC1)
P0.13/1.5D: C30.2, R5.1, SW_UP.2
P0.13/2.6C: U1.P$AD8 (P0.13)
P0.14/1.5D: C31.2, R8.1, SW_ENT.2
P0.14/2.7C: U1.P$AC9 (P0.14)
P0.19: U1.P$AC15 (P0.19)
P0.20: U1.P$AD16 (P0.20)
P0.21: U1.P$AC17 (P0.21)
P0.22: U1.P$AD18 (P0.22)
P0.23: U1.P$AC19 (P0.23)
P0.24: U1.P$AD20 (P0.24)
P0.25: U1.P$AC21 (P0.25)
P0.26: U1.P$G1 (P0.26)
P0.27: U1.P$H2 (P0.27)
P0.28: U1.P$B11 (P0.28/AIN4)
P0.29: U1.P$A10 (P0.29/AIN5)
P0.30: U1.P$B9 (P0.30/AIN6)
P0.31: U1.P$A8 (P0.31/AIN7)
P1.01/1.6C: Q2.1 (G), R_PWR_EPD1.1
P1.01/2.4B: U1.P$Y23 (P1.01)
P1.02/1.6C: C29.2, R7.1, SW_DN.2
P1.02/2.8C: U1.P$W24 (P1.02)
P1.03: U1.P$V23 (P1.03)
P1.04: U1.P$U24 (P1.04)
P1.05: U1.P$T23 (P1.05)
P1.06: U1.P$R24 (P1.06)
P1.07: U1.P$P23 (P1.07)
P1.09: U1.P$R1 (P1.09)
P1.10: U1.P$A20 (P1.10)
P1.11: U1.P$B19 (P1.11)
P1.12: U1.P$B17 (P1.12)
P1.13: U1.P$A16 (P1.13)
P1.14: U1.P$B15 (P1.14)
P1.15: U1.P$A14 (P1.15)
PMIC_INT: IC1.A1 (!INT), U1.P$T2 (P0.11)
PREVGH: D5.1 (K), EPD_C9.2, J1.21
PREVGL: D2.2 (A), EPD_C11.2, J1.23
RESE: J1.3, Q3.2 (S), R1_EP_DR.2
RESET: J2.6, TP_RESET.TP, U1.P$AC13 (P0.18/RESET)
SCK/1.5B: J1.13
SCK/2.2D: U1.P$A12 (P0.02/AIN0)
SCL/1.4C: IC2.C1 (SCL)
SCL/2.4C: IC1.B1 (SCL), IC3.12 (SCX), R4.1, R17.2, TP_SCL.TP, U1.P$M2 (P0.07), U3.7 (SCL)
SDA/1.4C: IC2.B2 (SDA)
SDA/2.4C: IC1.C1 (SDA), IC3.2 (SDX), R2.1, R18.2, TP_SDA.TP, U1.P$L1 (P0.06), U3.8 (SDA)
SWDCLK: J2.4, TP_SWDCLK.TP, U1.P$AA24 (SWDCLK)
SWDIO: J2.2, TP_SWDIO.TP, U1.P$AC24 (SWDIO)
SWO: TP_SWO.TP, U1.P$AD22 (P1.00)
VBAT/1.2A: C27.2, TP_VBAT.TP, U3.2 (CELL), U3.3 (VDD)
VBAT/2.5C: C37.2, IC1.C2 (BAT)
VBUS/1.5D: C42.1, C43.1, D3.5 (VBUS), J4.A4_B9 (VBUS), J4.A9_B4 (VBUS)
VBUS/2.6D: C21.1, C38.2, IC1.A2 (IN), U1.P$AD2 (VBUS)
VREG: C23.2, C24.2, C39.1, IC1.B2 (SYS), IC9.A1 (EN), IC9.A2 (VIN_1), IC9.A3 (VIN_2), TP_VREG.TP

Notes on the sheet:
SWD
DEC1
DEC3
DEC4_6
LiPo Charger
10k
DC/DC
1uF
0.1uF
3K3
IMU
E-Paper Display Connector
Fuel Gauge
E-Paper Drive Circuit
0.47
2.2
10K
USB C Connector & ESD Protection
5K1
DMG2305UX-7
Haptic Driver
Buttons
FTC252012SR47MBCA
P0.00/XL1
P0.01/XL2

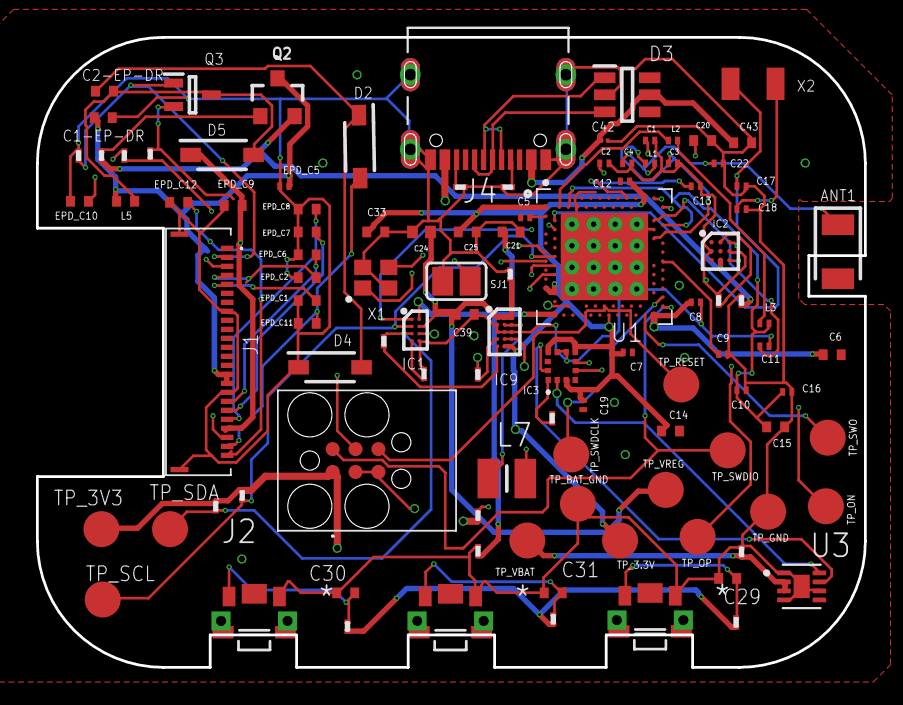
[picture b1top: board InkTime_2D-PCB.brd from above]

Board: 4 copper layers, 46.0 x 35.0 mm, 105 parts (0 on the bottom side), 64 nets.

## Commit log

2026-04-15 Fix 90 degree nets Fixes #2
2026-04-15 Add missing reference Fixes #1
2026-04-16 Fix antenna cutout and update X2 component library
    Fixes #4
    Fixes #9
2026-04-17 Fix nets and symbol naming inconsistencies
    Fixes #8
2026-04-17 Completed Ground Plane for the 4-layer routing
    Fixes #3
2026-04-17 Placed decoupling capacitors close to the associated pins
    Fixes #10
2026-04-18 Simplified Silkscreen and optimized routing areas
    Fixes #11 and Fixes #5
2026-04-21 Update Schematic and Upload PrintOut
2026-04-21 Update Manufacturing Files
2026-04-21 Revise README with project name and detailed architecture
    Updated project name from 'InkTIme' to 'InkTime' and added detailed sections on block diagram, bill of materials, hardware functionality, and technical architecture.

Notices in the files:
parts and their libraries:
InkTime_v5: COPYRIGHT: Copyright (C) 2025 Ultra Librarian. All rights reserved.
